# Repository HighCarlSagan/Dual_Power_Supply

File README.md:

# Universal PSU — 4A Dual-Output Power Supply

A compact mains-input dual-output bench supply built around an isolated AC-DC brick and two integrated buck modules. Provides clean, regulated 5 V and 3.3 V rails for hobby electronics — bench bringup, MCU dev boards, sensors, LEDs, and small actuator loads.

---

## Why I Built This

I wanted a single, always-on bench supply that I could leave plugged in and tap into for anything I'm prototyping: ESP32s, Pis, sensor breakouts, the Telegram-controlled lights board, whatever.

This was also a deliberate learning project on two fronts:

- **4-layer PCB layout for power applications** — getting the ground plane right, thermal management on the regulator footprints, and clean current return paths in a real-world design rather than a textbook example.
- **Mains-isolated module integration** — using a certified AC-DC brick lets me keep the dangerous side fully encapsulated while still building a useful, mains-powered project. A natural stepping stone before I take on a discrete flyback design later.

---

## Initial Requirements

These were the spec points I wrote down before any design work. The "Outcome" column shows what actually shipped.

| # | Requirement | Target | Outcome |
|---|---|---|---|
| 1 | Universal AC input | 110–230 V AC, 50/60 Hz | ✅ Met (IRM-60-15) |
| 2 | Output rail A | 5 V regulated | ✅ Met |
| 3 | Output rail B | 3.3 V regulated | ✅ Met |
| 4 | Continuous current per rail | 6 A | ⚠️ **4 A** — part ordered was TLVM14406 (4 A), not a 6 A variant. Sufficient for intended loads, scope kept. |
| 5 | Total power budget | ~60 W | ✅ Met (IRM-60-15 = 60 W headroom; DC-DC stage caps actual deliverable lower) |
| 6 | Form factor | Compact, no specific dimensions | ✅ 150 × 80 mm, 4-layer |
| 7 | Output protection (OCP, OVP) | TVS + fuse on outputs | ❌ **Missed in V1** — see [MkII Wishlist](#mkii-wishlist) |
| 8 | Status LEDs | Per-rail power-good indicators | ❌ **Missed in V1** — see [MkII Wishlist](#mkii-wishlist) |
| 9 | Reliability target | 3–4 years continuous service | TBD post-test |

---

## Specifications

| Parameter | Value |
|---|---|
| Input voltage | 110–230 V AC |
| Input frequency | 50 / 60 Hz |
| Intermediate rail | 15 V DC (internal only, see [Future Options](#future-options)) |
| Output 1 | 5 V @ 4 A |
| Output 2 | 3.3 V @ 4 A |
| Total output power | ~33 W deliverable from DC-DC stage<br>(60 W brick headroom) |
| PCB | 4-layer FR-4, 1.6 mm |
| Dimensions | 150 × 80 mm |
| Mounting | 4× M2 corner holes |
| Connectors | 4× 4-pin screw terminal blocks |

---

## Architecture

```
   AC Mains              Isolated brick           DC-DC stage              Outputs
  ┌─────────┐         ┌──────────────┐        ┌──────────────┐         ┌─────────┐
  │ 110-230 │────────▶│  IRM-60-15   │───15V─▶│ TLVM14406 #1 │────5V──▶│  J3     │
  │  V AC   │         │   60W AC-DC  │   │    └──────────────┘         └─────────┘
  └─────────┘         └──────────────┘   │    ┌──────────────┐         ┌─────────┐
                                         └───▶│ TLVM14406 #2 │────3.3V▶│  J4     │
                                              └──────────────┘         └─────────┘
```

The mains side is fully handled by the certified Mean Well IRM-60-15 brick. Everything on the PCB downstream is low-voltage DC, so the layout focused on thermal performance, ground-plane integrity, and switching-loop minimization rather than mains-side concerns.

---

## Key Components

| Reference | Part | Function |
|---|---|---|
| PS1 | Mean Well IRM-60-15 | 60 W universal-input AC-DC brick, 15 V output, fully isolated |
| PS2 | TI TLVM14406RCHR | Integrated 4 A SWIFT buck module, configured for 5 V |
| PS3 | TI TLVM14406RCHR | Integrated 4 A SWIFT buck module, configured for 3.3 V |
| J1–J4 | 4-pin screw terminals | Mains input, intermediate, and two output rails |

### Why the IRM-60 + TLVM14406 combo?

- **AC-DC brick over discrete flyback** — I wanted a reliable, working solution I could trust to leave running for years, without first having to learn off-line converter design, transformer winding, EMI compliance, and creepage/clearance. The IRM-60 is certified, isolated, and lets me focus the project on the DC-DC stage.
- **TLVM14406 over discrete switcher + inductor** — I'd worked with this family before. The integrated module collapses the inductor selection, compensation network design, and layout-critical switching loop into a known-good footprint. Fast path to a board that works.

---

## Connector Pinout

All four screw terminals share the same convention:

| Pin | Function |
|---|---|
| 1 | Power (V+) |
| 2 | Power (V+) |
| 3 | GND |
| 4 | GND |

Doubling power and ground pins lets each rail handle its rated current without exceeding terminal current limits and gives a cleaner mechanical termination for thicker wires.

| Connector | Use |
|---|---|
| J1 | AC mains input (Live / Neutral / Earth — see silkscreen) |
| J2 | 15 V intermediate (test point only — not for external loads in V1) |
| J3 | 5 V output |
| J4 | 3.3 V output |

---

## Repository Structure

```
universal-psu/
├── Exports/
│   ├── Gerber/                       # Production gerbers + drill files
│   ├── Photos/                       # Real PCB photos (added after assembly)
│   │   └── Testing/                  # Bench test photos & scope captures
│   ├── schematic.pdf                 # Full schematic export
│   ├── universal-psu-3dview-top.png  # PCB 3D render — top
│   ├── universal-psu-3dview-bot.png  # PCB 3D render — bottom
│   ├── universal-psu_bom.csv         # Bill of materials
│   ├── universal_psu_gerbers.zip     # Zipped gerbers for fab upload
│   └── universal-psu.net             # Netlist
├── Subsheets/
│   ├── DC_DC_Converter_5V.kicad_sch  # 5 V rail subsheet
│   └── DC_DC_Converter_3v3.kicad_sch # 3.3 V rail subsheet
├── libraries/                        # Custom KiCad symbols, footprints, 3D models
├── universal-psu.kicad_pro           # KiCad project
├── universal-psu.kicad_sch           # Top-level schematic
├── universal-psu.kicad_pcb           # PCB layout
├── LICENSE                           # CERN-OHL-P-2.0
└── README.md
```

---

## Bringup & Testing

> **Status:** PCBs back from fab, assembly in progress. Bringup test results will be posted in this section as they're collected.

### Planned bringup procedure

1. **Visual inspection** — solder bridges, especially around the AC-DC module and the screw terminal footprints
2. **Continuity check (power off)** — input-to-output isolation, no shorts on either rail
3. **Mains-up with no DC-side load** — verify 15 V intermediate rail comes up cleanly from the IRM-60 brick
4. **DC-DC bringup, no load** — verify 5 V and 3.3 V come up to spec (sanity-check the feedback divider math against measurement; resistor values to be verified during this step)
5. **Light load test** — 100 mA per rail, check ripple on a scope
6. **Stepped load test** — 0.5 A → 1 A → 2 A → 3 A → 4 A per rail, log:
   - DC output voltage (line/load regulation)
   - Output ripple (peak-to-peak)
   - Brick case temperature
   - TLVM14406 case temperature (thermal cam)
   - Input current draw (for a rough efficiency number)
7. **Thermal soak** — full load on both rails for 1 hour, log temperatures every 5 minutes

### Test results

*To be added in `Exports/Photos/Testing/` — scope captures, thermal images, and a bench-test summary table.*

| Test | Target | Measured | Notes |
|---|---|---|---|
| 5 V rail accuracy | 4.95 – 5.05 V | _TBD_ | |
| 3.3 V rail accuracy | 3.25 – 3.35 V | _TBD_ | |
| 5 V ripple @ 4 A | < 50 mV pp | _TBD_ | |
| 3.3 V ripple @ 4 A | < 50 mV pp | _TBD_ | |
| Brick temp @ full load | < 70 °C case | _TBD_ | |
| TLVM14406 temp @ 4 A | < 85 °C case | _TBD_ | |
| Line regulation | < 1 % | _TBD_ | |
| Load regulation | < 2 % | _TBD_ | |

---

## When To Use This Board

**Good fit:**
- Powering MCU dev boards (ESP32, RP2040, STM32 Nucleo, Pi Pico)
- Sensor breakouts, LCD modules, small displays
- LED strips and controllers (within 4 A budget)
- General benchtop hobby work where 5 V and 3.3 V are needed simultaneously

**Not a good fit:**
- Motor drives or anything inductive that kicks back significantly (no protection on V1)
- Audio circuits (no LC post-filtering for low-noise applications)
- Safety-critical or always-on industrial use (fuses and TVS missing on V1)
- Loads above 4 A continuous per rail

---

## Future Options

- **Expose 15 V intermediate as a third output** — already present internally, just needs a connector and trace fanned out. Useful for op-amp circuits, fan drives, or any project that wants a higher rail.
- **Output protection** — eFuse or polyfuse + TVS on each output rail.
- **Per-rail status LEDs** — power-good indicators tied to the TLVM14406 PG output.
- **3D-printed enclosure** — open-frame is fine for the bench, but a printed case would make this safer to leave plugged in long-term.

---

## MkII Wishlist

Honest list of what V1 missed that V2 should fix:

1. **Output protection** — no TVS, no fuses, no eFuses. A short on either output goes directly to the buck module's internal protection only.
2. **Status LEDs** — no visible indication that either rail is alive.
3. **Mounting hole placement** — corner holes are too close to the board edge, making the board awkward to mount in any standard enclosure. V2 should use rounded corners and proper standoff offsets.
4. **Silkscreen labeling** — connector pin functions need clearer markings on the board face.
5. **15 V tap connector** — needs a header.

---

## Manufacturing

Boards fabricated as standard 4-layer FR-4. Gerbers in `Exports/Gerber/` are compatible with JLCPCB, PCBWay, OSHPark, and similar fab houses.

**Fab specs used:**
- 4-layer, 1.6 mm FR-4
- 1 oz copper outer + inner
- ENIG surface finish recommended for finer pitch parts
- Default solder mask, white silkscreen

---

## Safety

> ⚠️ **DANGER — MAINS VOLTAGE**
>
> This board operates at 110–230 V AC. The mains-side energy can be lethal.
>
> The mains side is encapsulated inside the certified IRM-60-15 brick — no exposed mains-voltage traces exist on the PCB itself once the brick is mounted. However, the screw terminal carrying mains input (J1) and the brick's own input pins are exposed and must be enclosed before powering up.
>
> - Never operate without proper insulation around J1 and the brick's input side
> - Do not bypass or modify the AC-DC brick
> - Use a current-limited isolation transformer for first power-on if you have one available
> - Comply with local electrical codes
> - Not for medical, life-support, or safety-critical use
>
> **The author assumes no liability for injury, death, or property damage.**

---

## License

This project is licensed under the **CERN Open Hardware Licence Version 2 — Permissive (CERN-OHL-P-2.0)**.

You are free to:
- Use, modify, and distribute the design — commercially or non-commercially
- Create derivative works under any license you choose
- Use without sharing modifications back upstream

You must:
- Retain the original license notice and attribution

See [LICENSE](LICENSE) for the full text.

---

## Used By

This board powers the following projects in my portfolio:
- [PC_and_Light_Controller](https://github.com/HighCarlSagan/PC_and_Light_Controller) — Telegram-controlled UPS button + LED switching

---

## Author

**Mayank S (HighCarlSagan)** — [GitHub @HighCarlSagan](https://github.com/HighCarlSagan) · [highcarlsagan.dev](https://highcarlsagan.dev)

Designed: December 2025 · Boards back: April 2026 · Bringup: in progress

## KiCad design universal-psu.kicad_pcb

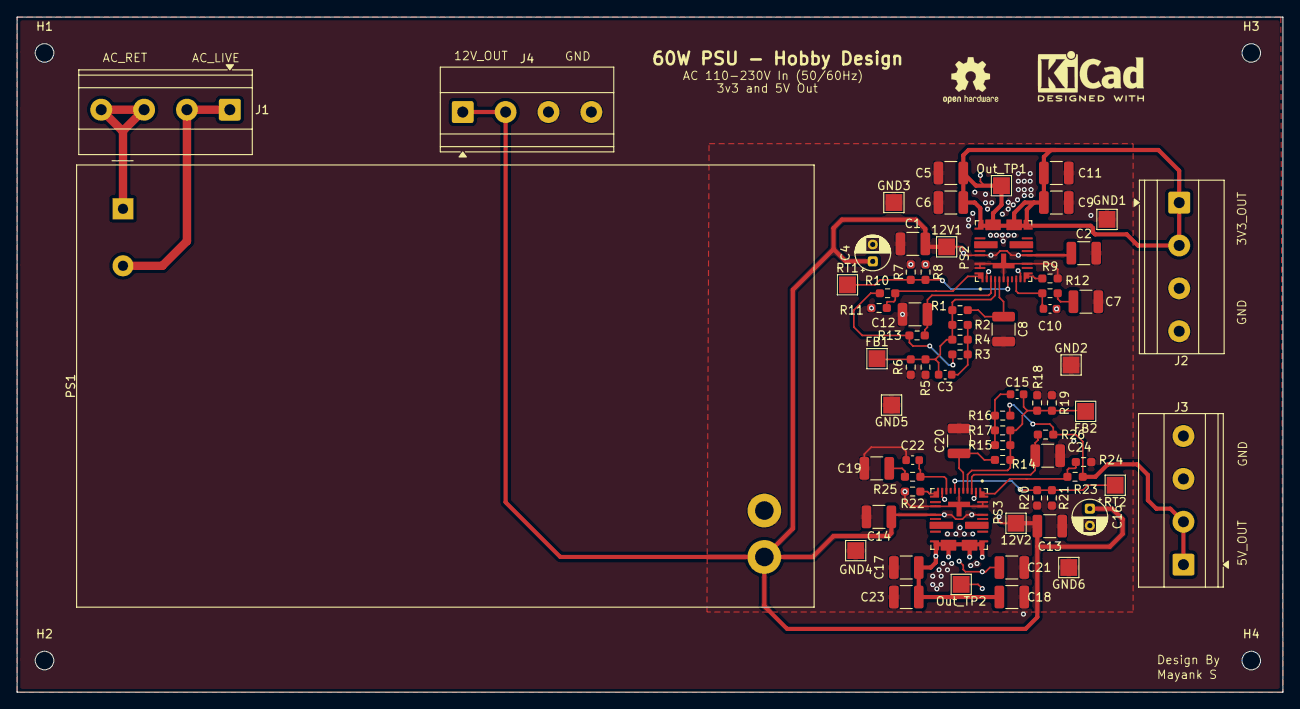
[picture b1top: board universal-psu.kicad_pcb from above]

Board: 4 copper layers, 150.0 x 80.0 mm, 75 parts (0 on the bottom side), 26 nets.

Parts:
12V1, 12V2: 12V; TestPoint_Pad_2.0x2.0mm
C1, C2, C13, C14: 10u_50V_1210; C_1210_3225Metric
C3, C10, C15, C22: 47n_16V_0603; C_0603_1608Metric
C4, C16: 100u_50V_1210; CP_Radial_D4.0mm_P2.00mm
C5, C6, C9, C11, C17, C18, C21, C23: 22u_25V_1210; C_1210_3225Metric
C7, C19: 2.2n_25V_1210; C_1210_3225Metric
C8, C12, C20, C24: 1u_25V_1210; C_1210_3225Metric
FB1, FB2: FB; TestPoint_Pad_2.0x2.0mm
GND1, GND2, GND3, GND4, GND5, GND6: GND; TestPoint_Pad_2.0x2.0mm
H1, H2, H3, H4: MH_Pad_MP; MountingHole_2.2mm_M2
J1, J2, J3, J4: Screw_Terminal_01x04; TerminalBlock_Phoenix_MKDS-1,5-4-5.08_1x04_P5.08mm_Horizont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
Out_TP1, Out_TP2: 5V; TestPoint_Pad_2.0x2.0mm
PS1: IRM-60-15; Converter_ACDC_MeanWell_IRM-60-xx_THT
PS2, PS3: TLVM14406RCHR; CONV_TLVM14406RCHR
R1, R5, R10, R11, R14, R18, R23, R24: 10k_0.21W_0603; R_0603_1608Metric_Pad0.98x0.95mm_HandSolder
R2, R7, R15, R20: 31.6k_0.21W_0603; R_0603_1608Metric_Pad0.98x0.95mm_HandSolder
R3, R16: 100_0.21W_0603; R_0603_1608Metric_Pad0.98x0.95mm_HandSolder
R4, R17: 52.3k_0.21W_0603; R_0603_1608Metric_Pad0.98x0.95mm_HandSolder
R6, R13, R19, R26: 0_0.21W_0603; R_0603_1608Metric_Pad0.98x0.95mm_HandSolder
R8, R21: 7.15k_0.21W_0603; R_0603_1608Metric_Pad0.98x0.95mm_HandSolder
R9, R22: 9.53k_0.21W_0603; R_0603_1608Metric_Pad0.98x0.95mm_HandSolder
R12, R25: 11k_0.21W_0603; R_0603_1608Metric_Pad0.98x0.95mm_HandSolder
RT1, RT2: RT; TestPoint_Pad_2.0x2.0mm

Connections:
+3V3: C5.1, C6.1, C9.1, C11.1, J2.1, J2.2, Out_TP1.1 (1_1), PS2.18 (VOUT/VOUT2), PS2.19 (VOUT/VOUT2__1), PS2.20 (VOUT/VOUT1), PS2.21 (VOUT/VOUT1__1), R3.1, R10.1, R13.1
+5V: C17.1, C18.1, C21.1, C23.1, J3.1, J3.2, Out_TP2.1 (1_1), PS3.18 (VOUT/VOUT2), PS3.19 (VOUT/VOUT2__1), PS3.20 (VOUT/VOUT1), PS3.21 (VOUT/VOUT1__1), R16.1, R23.1, R26.1
+12V: 12V1.1 (1_1), 12V2.1 (1_1), C1.1, C2.1, C4.1, C13.1, C14.1, C16.1, J4.1, J4.2, PS1.3 (+Vout), PS2.14 (VIN2), PS2.25 (VIN1), PS3.14 (VIN2), PS3.25 (VIN1)
/DC_DC_Converter_3v3/COMP: C10.1, PS2.9 (COMP/VOSNS2), R12.1
/DC_DC_Converter_3v3/CONFIG: PS2.11 (CONFIG), R9.1
/DC_DC_Converter_3v3/Enable: PS2.2 (EN1), PS2.10 (EN2)
/DC_DC_Converter_3v3/FB: C3.2, FB1.1 (1_1), PS2.4 (FB1), R1.2, R2.2, R4.2, R5.1, R6.1
/DC_DC_Converter_3v3/PG: PS2.1 (PG1), R10.2, R11.1
/DC_DC_Converter_3v3/RT: PS2.7 (RT), R7.1, R8.1, RT1.1 (1_1)
/DC_DC_Converter_3v3/Vcc: C8.1, PS2.5 (VCC), R1.1
/DC_DC_Converter_3v3/Vosns: C12.1, PS2.3 (BIAS_VOSNS1), R13.2
/DC_DC_Converter_5V/COMP: C22.1, PS3.9 (COMP/VOSNS2), R25.1
/DC_DC_Converter_5V/CONFIG: PS3.11 (CONFIG), R22.1
/DC_DC_Converter_5V/Enable: PS3.2 (EN1), PS3.10 (EN2)
/DC_DC_Converter_5V/FB: C15.2, FB2.1 (1_1), PS3.4 (FB1), R14.2, R15.2, R17.2, R18.1, R19.1
/DC_DC_Converter_5V/PG: PS3.1 (PG1), R23.2, R24.1
/DC_DC_Converter_5V/RT: PS3.7 (RT), R20.1, R21.1, RT2.1 (1_1)
/DC_DC_Converter_5V/Vcc: C20.1, PS3.5 (VCC), R14.1
/DC_DC_Converter_5V/Vosns: C24.1, PS3.3 (BIAS_VOSNS1), R26.2
AC_In_Live: J1.3, J1.4, PS1.1 (AC/L)
AC_In_Neutral: J1.1, J1.2, PS1.2 (AC/N)
GND: C1.2, C2.2, C4.2, C5.2, C6.2, C7.2, C8.2, C9.2, C10.2, C11.2, C12.2, C13.2, C14.2, C16.2, C17.2, C18.2, C19.2, C20.2, C21.2, C22.2, C23.2, C24.2, GND1.1 (1_1), GND2.1 (1_1), GND3.1 (1_1), GND4.1 (1_1), GND5.1 (1_1), GND6.1 (1_1), J2.3, J2.4, J3.3, J3.4, J4.3, J4.4, PS1.4 (-Vout), PS2.6 (AGND), PS2.13 (PGND), PS2.26 (PGND__1), PS2.27 (GND), PS2.28 (PGND__2), PS3.6 (AGND), PS3.13 (PGND), PS3.26 (PGND__1), PS3.27 (GND), PS3.28 (PGND__2), R5.2, R6.2, R7.2, R8.2, R9.2, R11.2, R18.2, R19.2, R20.2, R21.2, R22.2, R24.2
unnamed: C3.1, R2.1, R3.2, R4.1
unnamed: C7.1, R12.2
unnamed: C15.1, R15.1, R16.2, R17.1
unnamed: C19.1, R25.2

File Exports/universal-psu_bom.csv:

"Reference","Qty","Value","DNP","Exclude from BOM","Exclude from Board","Footprint","Datasheet","MANUFACTURER","Manufacturer Part Number","Price","Vendor","Vendor Link","Description","Vendor Part Number"
"12V1,12V2","2","12V","","","","TestPoint:TestPoint_Pad_2.0x2.0mm","","","","","","","test point",""
"C1,C2,C13,C14","4","10u_50V_1210","","","","Capacitor_SMD:C_1210_3225Metric","https://www.yageogroup.com/content/datasheet/asset/file/KEM_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","KEMET","C1210C106M3RACTU","28.2","","https://www.digikey.in/en/products/detail/kemet/C1210C106M3R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","10 µF ±20% 25V Ceramic Capacitor X7R 1210 (3225 Metric)","399-C1210C106M3RACTUCT-ND"
"C3,C10,C15,C22","4","47n_16V_0603","","","","Capacitor_SMD:C_0603_1608Metric","https://mm.digikey.com/Volume0/opasdata/d220001/medias/docus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","KEMET","CL10B473KO8NNNC","4.78","","https://www.digikey.in/en/products/detail/kemet/C0603C473K3R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","0.047 µF ±10% 16V Ceramic Capacitor X7R 0603 (1608 Metric)","1276-2079-1-ND"
"C4,C16","2","100u_50V_1210","","","","Capacitor_THT:CP_Radial_D4.0mm_P2.00mm","https://www.yageogroup.com/content/datasheet/asset/file/KEM_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","KEMET","EEV107M050S9MAA","41.6","","https://www.digikey.in/en/products/detail/kemet/EEV107M050S9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","100 µF 50 V Aluminum Electrolytic Capacitors Radial, Can - SMD 2000 Hrs @ 105°C","399-EEV107M050S9MAACT-ND"
"C5,C6,C9,C11,C17,C18,C21,C23","8","22u_25V_1210","","","","Capacitor_SMD:C_1210_3225Metric","https://search.murata.co.jp/Ceramy/image/img/A01X/G101/ENG/G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","KEMET","GRM32ER71E226ME15L","42.04","","https://www.digikey.in/en/products/detail/murata-electronics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","22 µF ±20% 25V Ceramic Capacitor X7R 1210 (3225 Metric)","490-10758-1-ND"
"C7,C19","2","2.2n_25V_1210","","","","Capacitor_SMD:C_1210_3225Metric","https://search.murata.co.jp/Ceramy/image/img/A01X/G101/ENG/G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","KEMET","C0603C473K3RACTU","4.78","","https://www.digikey.in/en/products/detail/kemet/C0603C473K3R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","0.047 µF ±10% 25V Ceramic Capacitor X7R 0603 (1608 Metric)","399-C0603C473K3RACTUCT-ND"
"C8,C12,C20,C24","4","1u_25V_1210","","","","Capacitor_SMD:C_1210_3225Metric","https://www.yageogroup.com/content/datasheet/asset/file/KEM_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","KEMET","C1210C105K3RACTU","100","","https://www.digikey.in/en/products/detail/kemet/C1210C105K3R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","1 µF ±10% 25V Ceramic Capacitor X7R 1210 (3225 Metric)","399-C1210C105K3RACTUCT-ND"
"FB1,FB2","2","FB","","","","TestPoint:TestPoint_Pad_2.0x2.0mm","","","","","","","test point",""
"GND1,GND2,GND3,GND4,GND5,GND6","6","GND","","","","TestPoint:TestPoint_Pad_2.0x2.0mm","","","","","","","test point",""
"J1,J2,J3","3","Screw_Terminal_01x04","","","","TerminalBlock_Phoenix:TerminalBlock_Phoenix_MKDS-1,5-4-5.08_1x04_P5.08mm_Horizontal","https://www.phoenixcontact.com/us/products/1715048/pdfhttps: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","Phoenix Contact","1715048","257","","https://www.digikey.in/en/products/detail/phoenix-contact/17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","4 Position Wire to Board Terminal Block Horizontal with Board 0.197"" (5.00mm) Through Hole","277-1260-ND"
"Out_TP1,Out_TP2","2","5V","","","","TestPoint:TestPoint_Pad_2.0x2.0mm","","","","","","","test point",""
"PS1","1","IRM-60-15","","","","Converter_ACDC:Converter_ACDC_MeanWell_IRM-60-xx_THT","http://www.meanwellusa.com/productPdf.aspx?i=687","MEAN WELL USA Inc.","IRM-60-12","1327","","https://www.digikey.in/en/products/detail/mean-well-usa-inc/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","15V, 4A, 60W, Isolated, AC-DC, IRM60","1866-3063-ND"
"PS2,PS3","2","TLVM14406RCHR","","","","footprints:CONV_TLVM14406RCHR","https://www.ti.com/lit/ds/symlink/tlvm14404.pdf?ts=1731607059072","Texas Instruments","TLVM14406RCHR","742","","https://www.digikey.in/en/products/detail/texas-instruments/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","Non-Isolated PoL Module DC DC Converter 2 Output 0.8 ~ 9V 3A, 3A 3V - 36V Input","296-TLVM14406RCHRCT-ND"
"R1,R5,R10,R11,R14,R18,R23,R24","8","10k_0.21W_0603","DNP","","","Resistor_SMD:R_0603_1608Metric_Pad0.98x0.95mm_HandSolder","https://www.vishay.com/docs/20043/crcwhpe3.pdf","Vishay Dale","CRCW060310K0FKEAHP","6.01","","https://www.digikey.in/en/products/detail/vishay-dale/CRCW06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","10 kOhms ±1% 0.333W, 1/3W Chip Resistor 0603 (1608 Metric) Automotive AEC-Q200, Pulse Withstanding Thick Film","541-10.0KSCT-ND"
"R2,R7,R15,R20","4","31.6k_0.21W_0603","","","","Resistor_SMD:R_0603_1608Metric_Pad0.98x0.95mm_HandSolder","https://www.vishay.com/docs/28773/crcwce3.pdf","Vishay Dale","CRCW060331K6FKEAC","2.56","","https://www.digikey.in/en/products/detail/vishay-dale/CRCW06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","31.6 kOhms ±1% 0.1W, 1/10W Chip Resistor 0603 (1608 Metric) Thick Film","541-5351-1-ND"
"R3,R16","2","100_0.21W_0603","","","","Resistor_SMD:R_0603_1608Metric_Pad0.98x0.95mm_HandSolder","https://www.vishay.com/docs/20043/crcwhpe3.pdf","Vishay Dale","CRCW0603100RFKEAHP","6.01","","https://www.digikey.in/en/products/detail/vishay-dale/CRCW06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","100 Ohms ±1% 0.333W, 1/3W Chip Resistor 0603 (1608 Metric) Automotive AEC-Q200, Pulse Withstanding Thick Film","541-100SCT-ND"
"R4,R17","2","52.3k_0.21W_0603","","","","Resistor_SMD:R_0603_1608Metric_Pad0.98x0.95mm_HandSolder","https://www.vishay.com/docs/28773/crcwce3.pdf","Vishay Dale","CRCW060352K3FKEAC","2.56","","https://www.digikey.in/en/products/detail/vishay-dale/CRCW06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","52.3 kOhms ±1% 0.1W, 1/10W Chip Resistor 0603 (1608 Metric) Thick Film","541-5470-1-ND"
"R6,R13,R19,R26","4","0_0.21W_0603","DNP","","","Resistor_SMD:R_0603_1608Metric_Pad0.98x0.95mm_HandSolder","https://www.vishay.com/docs/20043/crcwhpe3.pdf","Vishay Dale","CRCW06030000Z0EAHP","4.86","","https://www.digikey.in/en/products/detail/vishay-dale/CRCW06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,https://www.digikey.in/en/products/detail/vishay-dale/CRCW06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","0 Ohms Jumper Chip Resistor 0603 (1608 Metric) Automotive AEC-Q200, Pulse Withstanding Thick Film","541-0.0SBCT-ND"
"R8,R21","2","7.15k_0.21W_0603","","","","Resistor_SMD:R_0603_1608Metric_Pad0.98x0.95mm_HandSolder","https://www.vishay.com/docs/20043/crcwhpe3.pdf","Vishay Dale","CRCW06037K15FKEAHP","6.9","","https://www.digikey.in/en/products/detail/vishay-dale/CRCW06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","Resistor","541-CRCW06037K15FKEAHPCT-ND"
"R9,R22","2","9.53k_0.21W_0603","","","","Resistor_SMD:R_0603_1608Metric_Pad0.98x0.95mm_HandSolder","https://www.vishay.com/docs/28773/crcwce3.pdf","Vishay Dale","CRCW06039K53FKEAC","2.56","","https://www.digikey.in/en/products/detail/vishay-dale/CRCW06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","9.53 kOhms ±1% 0.1W, 1/10W Chip Resistor 0603 (1608 Metric) Thick Film","541-5606-1-ND"
"R12,R25","2","11k_0.21W_0603","","","","Resistor_SMD:R_0603_1608Metric_Pad0.98x0.95mm_HandSolder","https://www.vishay.com/docs/28773/crcwce3.pdf","Vishay Dale","CRCW060311K0FKEAC","2.56","","https://www.digikey.in/en/products/detail/vishay-dale/CRCW06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","11 kOhms ±1% 0.1W, 1/10W Chip Resistor 0603 (1608 Metric) Thick Film","541-5146-1-ND"
"RT1,RT2","2","RT","","","","TestPoint:TestPoint_Pad_2.0x2.0mm","","","","","","","test point",""

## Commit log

2025-12-23 Initial commit: Universal PSU KiCad project
2025-12-23 Remove .history from tracking
2025-12-23 Add comprehensive README with project specifications
2025-12-23 ReadMe author updates
2025-12-24 Layout import and schema fixes.
2025-12-24 layout changes
2025-12-25 more layout
2025-12-25 Layout closed, some DRC conflicts remain.
2025-12-25 hopefully final design output, time for manufacturing
2025-12-25 docs: Add comprehensive README with specs, safety warnings, and project structure with license on the silkscreen cos why not
2025-12-25 updated images
2025-12-27 minor fixes
2025-12-27 STEP file added
2025-12-28 silkscreen and one part footprint and part number change for C3, C10, C15 and C22
2025-12-28 Cleanup
2026-01-28 Connector change and silkscreen
2026-01-28 Gerbers and images updated
2026-02-01 Manufacturing Readiness
2026-02-06 final final manufacturing output
2026-02-06 minor pre fab edits
2026-05-10 docs: rewrite README with project structure, requirements table, and bringup plan; switch to CERN-OHL-P-2.0
2026-05-10 minor fixes on readme
